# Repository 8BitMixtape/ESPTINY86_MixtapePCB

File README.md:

# ESPTINY86_MixtapePCB

See more about the ESPTINY86 on https://github.com/esptiny86

# Where to get it

http://shop.8bitmixtape.cc/product/esptiny86-wifi-32bit-mixtape/

# Make Your Own 

## Preview of PCB gerber files

## How to solder it

Check the parts placement .pdf and warm up your soldering iron

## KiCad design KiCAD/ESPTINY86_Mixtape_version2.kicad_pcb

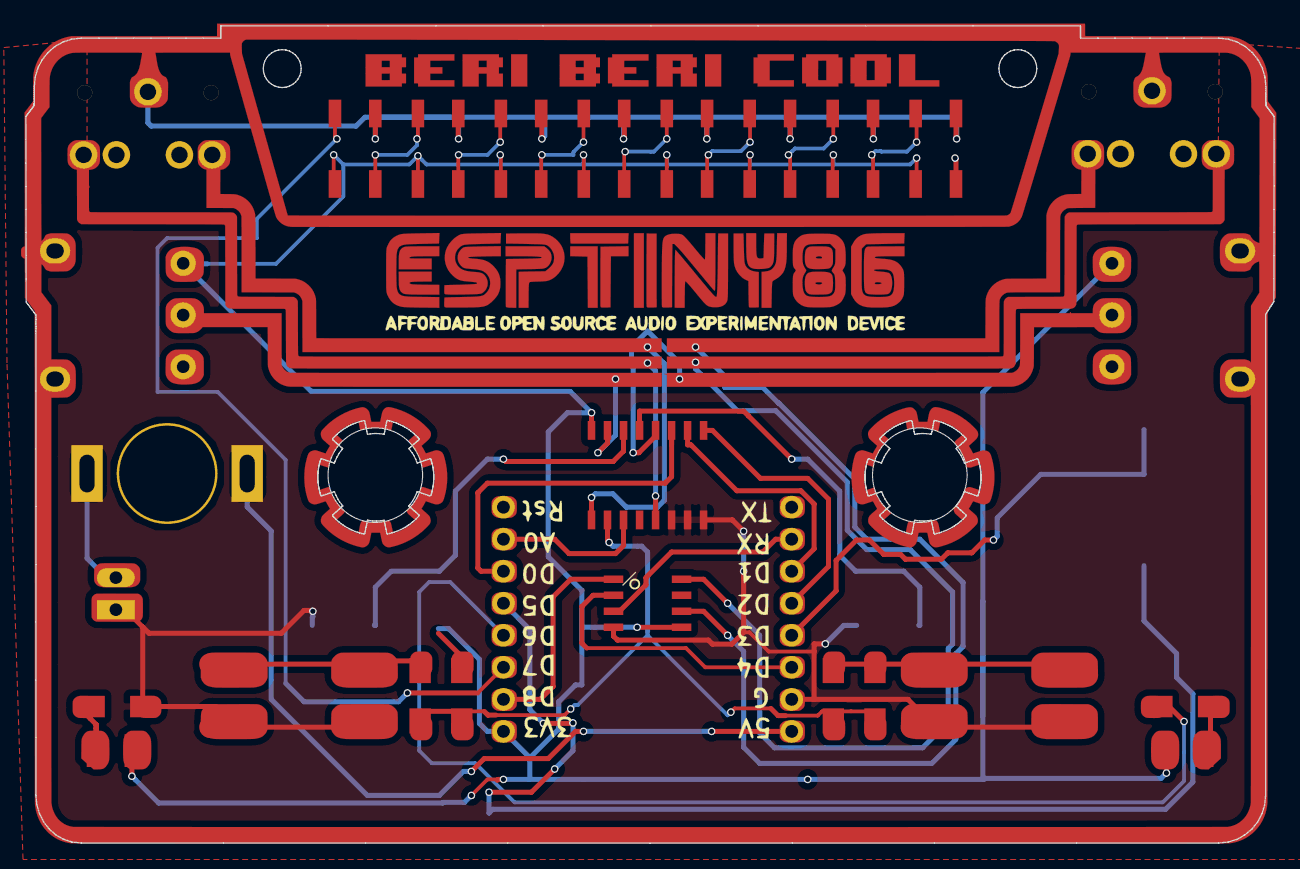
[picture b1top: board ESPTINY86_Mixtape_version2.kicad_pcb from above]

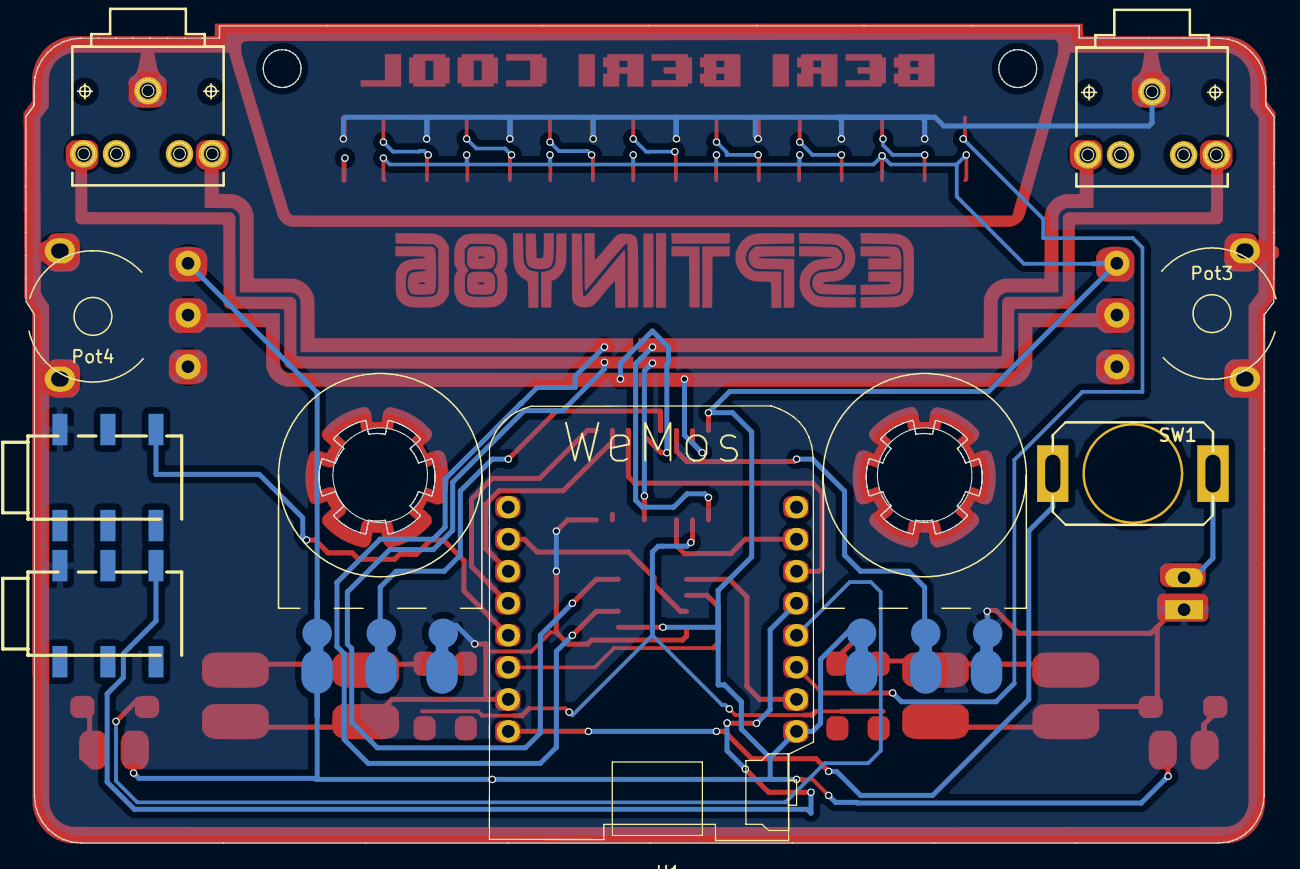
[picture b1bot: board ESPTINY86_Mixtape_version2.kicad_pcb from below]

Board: 2 copper layers, 99.0 x 64.8 mm, 32 parts (8 on the bottom side), 35 nets.

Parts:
Coconut: LOGO; Coconut_Logo_small_Mask
D1, D2: LED; TopLED_2835
IC1: 4051; 4xxx_SOIC-16W_Pitch1.27mm
IC2: DAC7513_DCN; SOIC-8_3.9x4.9mm_Pitch1.27mm
J1: Bat_EXT; Bat_connector+-
Jack1, Jack3: JACK_TRS_6PINS; AUDIO-Jack_3.5mm_5Pin
Jack2, Jack4: JACK_TRS_6PINS; AUDIO-JACK-3.5mm_SMD_noHole
NEO1, NEO2, NEO3, NEO4, NEO5, NEO6, NEO7, NEO8: LED_SK6813; Mixtape_NEO_WS2812B
Pot1: 10k_big; Potentiometer_backPads_noHole
Pot2: 10k; Potentiometer_backPads_noHole
Pot3: 10k; Potentiometer_wheel_inv
Pot4: 10k; Potentiometer_wheel
R1, R2: R; R_1206_Mixtape
R3, R3#2: 22k; R_1206_Mixtape
R4, R5: 10k; R_1206_Mixtape
SW1: SW_SPST; Push_SWITCH_hole
SW2, SW3: SW_Push; SW_PUSH-12mm_3D_SMD-top
U1: WeMos_mini; WeMOS_ESP

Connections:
+3V3: D1.2, D2.2, IC1.16, IC2.5, NEO1.1, NEO2.1, NEO3.1, NEO4.1, NEO5.1, NEO6.1, NEO7.1, NEO8.1, Pot1.1, Pot2.1, Pot3.1, Pot4.1, R4.1, U1.16
+5V: SW1.2, U1.1
+BATT: J1.1, SW1.1
Buttons: IC1.2, R3.2, R3#2.2, R4.2, R5.2
CV1: IC1.1, Jack3.2
CV2: IC1.5, Jack3.3
D3: Jack2.2, U1.4
D5: Jack4.2, U1.12
GND: IC1.6, IC1.7, IC1.8, IC2.4, J1.2, Jack1.1, Jack2.1, Jack3.1, Jack4.1, NEO1.3, NEO2.3, NEO3.3, NEO4.3, NEO5.3, NEO6.3, NEO7.3, NEO8.3, Pot1.3, Pot2.3, Pot3.3, Pot4.3, R2.1, SW2.2, SW3.2, U1.2
L-Out: IC2.6, Jack1.3
Led1_pulldown: R1.2, U1.13
NEO-Pixel: NEO8.4, U1.14
unnamed: D1.1, R1.1
unnamed: D2.1, R2.2
unnamed: IC1.3, U1.10
unnamed: IC1.9, U1.5
unnamed: IC1.10, U1.6
unnamed: IC1.11, U1.11
unnamed: IC2.1, U1.15
unnamed: IC2.3, U1.7
unnamed: NEO1.4, NEO2.2
unnamed: NEO2.4, NEO3.2
unnamed: NEO3.4, NEO4.2
unnamed: NEO4.4, NEO5.2
unnamed: NEO5.4, NEO6.2
unnamed: NEO6.4, NEO7.2
unnamed: NEO7.4, NEO8.2
unnamed: R3.1, R3#2.1, SW3.1
unnamed: R5.1, SW2.1
Pot1: IC1.13, Pot1.2
Pot2: IC1.14, Pot2.2
Pot3: IC1.15, Pot3.2
Pot4: IC1.12, Pot4.2
R-Out: IC2.8, Jack1.2
problem: IC2.2, U1.3

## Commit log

2018-12-11 Fixed~ Board KiCAD
2018-12-11 testing some design elements
2018-12-13 fixing the schematic
2019-03-10 adding parts s placement
2019-03-10 schematics corrected
2019-03-10 edit readme
2019-03-10 adding fake BOM
2019-03-10 kitspace ready
2019-03-10 fixing BOM
